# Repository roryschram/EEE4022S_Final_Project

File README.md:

## LoRa Based Communication System for Radiosonde Applications
### By Rory Schram

Welcome to my final year project GitHub page. This project focussed on the design and implementation of a LoRa-based radiosonde module for a weather balloon. Project files can be found in their respective folders, including all software, schematics, and PCB designs, for the transmission and receiver modules.

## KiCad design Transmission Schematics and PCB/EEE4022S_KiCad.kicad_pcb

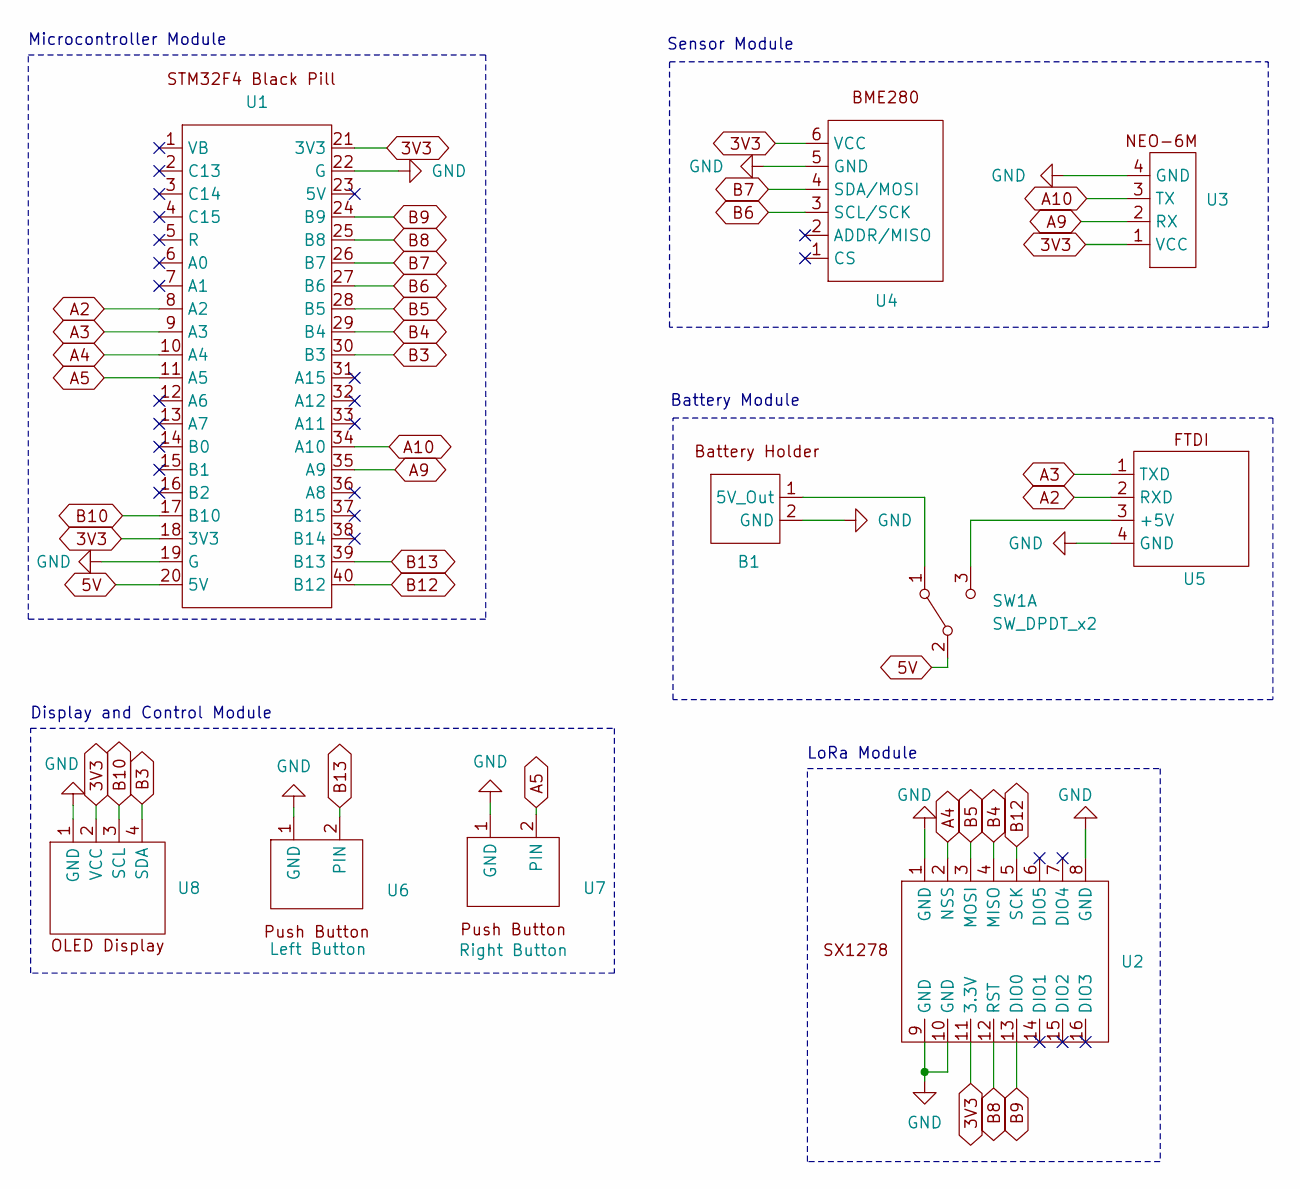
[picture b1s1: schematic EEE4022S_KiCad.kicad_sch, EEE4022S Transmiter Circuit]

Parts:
B1: Battery HolderCharger
SW1: SW_DPDT_x2
U1: STM32f4_Black_Pill
U2: SX1278
U3: NEO-6M
U4: BME280
U5: FTDI
U6: Left Button; Push Button
U7: Right Button; Push Button
U8: OLED Display

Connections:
3V3: U1.18 (3V3), U1.21 (3V3), U2.11 (3.3V), U3.1 (VCC), U4.6 (VCC), U8.2 (VCC)
5V: B1.1 (5V_Out), SW1.1 (A), SW1.2 (B), SW1.3 (C), U1.20 (5V), U5.3 (+5V)
A2: U1.8 (A2), U5.2 (RXD)
A3: U1.9 (A3), U5.1 (TXD)
A4: U1.10 (A4), U2.2 (NSS)
A5: U1.11 (A5), U7.2 (PIN)
A9: U1.35 (A9), U3.2 (RX)
A10: U1.34 (A10), U3.3 (TX)
B3: U1.30 (B3), U8.4 (SDA)
B4: U1.29 (B4), U2.4 (MISO)
B5: U1.28 (B5), U2.3 (MOSI)
B6: U1.27 (B6), U4.3 (SCL/SCK)
B7: U1.26 (B7), U4.4 (SDA/MOSI)
B8: U1.25 (B8), U2.12 (RST)
B9: U1.24 (B9), U2.13 (DIO0)
B10: U1.17 (B10), U8.3 (SCL)
B12: U1.40 (B12), U2.5 (SCK)
B13: U1.39 (B13), U6.2 (PIN)
GND: B1.2 (GND), U1.19 (G), U1.22 (G), U2.1 (GND), U2.8 (GND), U2.9 (GND), U2.10 (GND), U3.4 (GND), U4.5 (GND), U5.4 (GND), U6.1 (GND), U7.1 (GND), U8.1 (GND)

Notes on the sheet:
LoRa Module
Display and Control Module
Sensor Module
Microcontroller Module
Battery Module

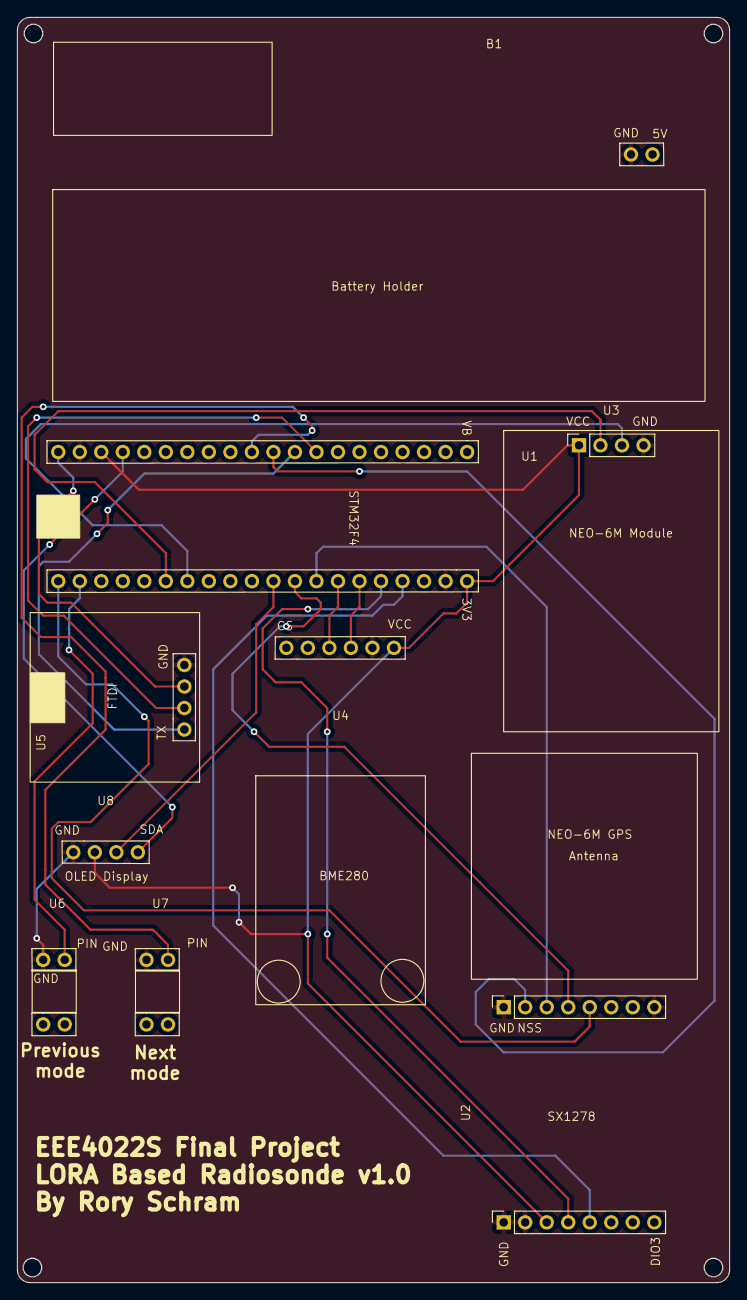
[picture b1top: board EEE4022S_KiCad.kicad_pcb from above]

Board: 2 copper layers, 84.0 x 149.3 mm, 9 parts (0 on the bottom side), 19 nets.

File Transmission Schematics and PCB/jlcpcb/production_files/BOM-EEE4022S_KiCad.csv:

Comment,Designator,Footprint,LCSC
~,U5,FTDI,
~,U3,NEO-6M,
Left Button,U6,Push Button,
~,U4,BME280,
Right Button,U7,Push Button,
~,B1,Battery HolderCharger,
~,U1,STM32f4_Black_Pill,
~,U8,OLED Display,
~,U2,SX1278,

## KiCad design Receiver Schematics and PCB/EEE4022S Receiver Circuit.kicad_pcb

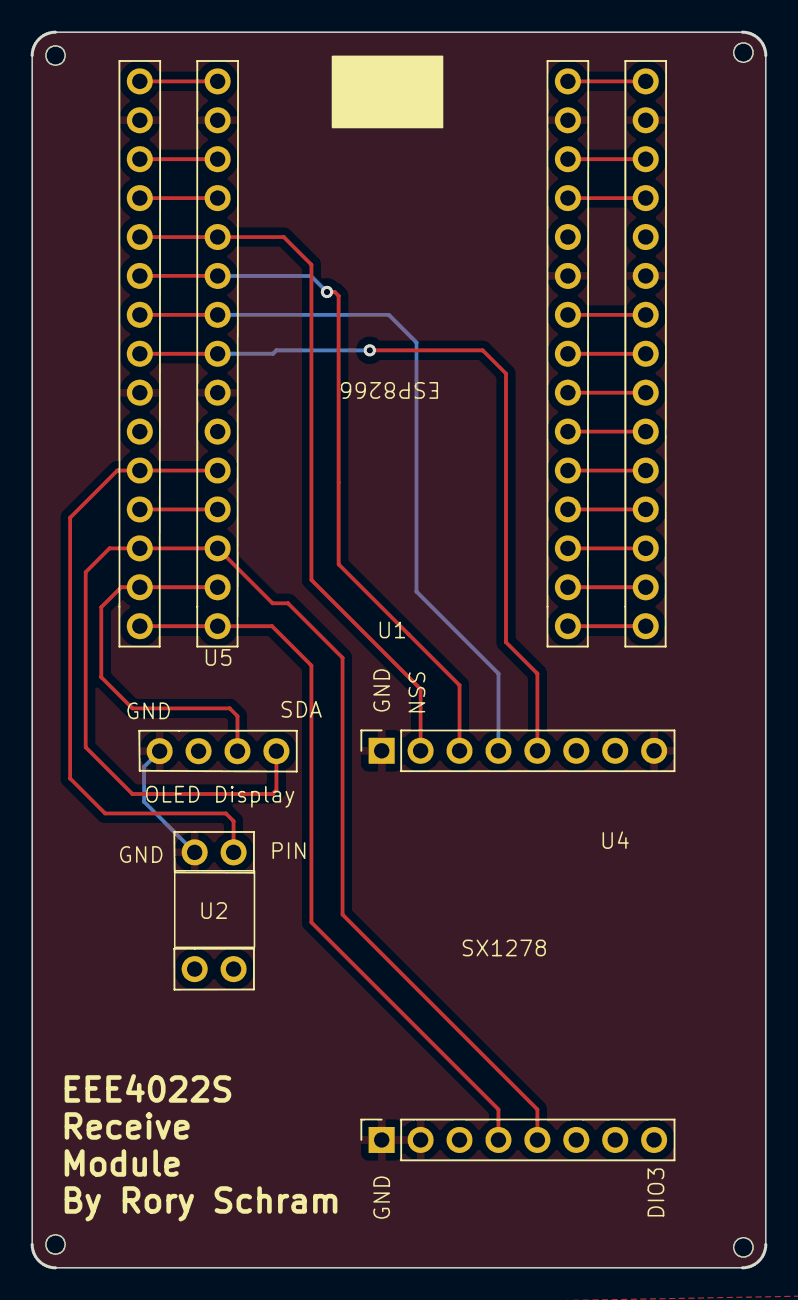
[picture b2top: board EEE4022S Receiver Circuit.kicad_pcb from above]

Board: 2 copper layers, 47.9 x 80.6 mm, 4 parts (0 on the bottom side), 10 nets.

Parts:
U1: ESP8266
U2: Navigator Button; Push Button
U4: SX1278
U5: OLED Display

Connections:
3V3: U1.11 (3V3), U1.21 (3V3), U4.11 (3.3V), U5.2 (VCC)
D0: U1.16 (D0), U4.12 (RST)
D1: U1.17 (D1), U5.3 (SCL)
D2: U1.18 (D2), U4.13 (DIO0), U5.4 (SDA)
D4: U1.20 (D4), U2.2 (PIN)
D5: U1.23 (D5), U4.5 (SCK)
D6: U1.24 (D6), U4.4 (MISO)
D7: U1.25 (D7), U4.3 (MOSI)
D8: U1.26 (D8), U4.2 (NSS)
GND: U1.10 (GND), U1.14 (GND), U1.22 (GND), U1.29 (GND), U2.1 (GND), U4.1 (GND), U4.8 (GND), U4.9 (GND), U4.10 (GND), U5.1 (GND)

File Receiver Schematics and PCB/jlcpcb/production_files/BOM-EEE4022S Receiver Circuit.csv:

Comment,Designator,Footprint,LCSC
~,U1,ESP8266,
~,U4,SX1278,
Navigator Button,U2,Push Button,
~,U5,OLED Display,

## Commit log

2023-09-21 First commit with GPS working
2023-09-21 Did a build on the code
2023-09-21 Implemented altitude measurement
2023-09-25 Transmission working perfectly now
2023-09-27 Fixed Lora Mdule with reset low issue
2023-10-04 Working Build
2023-10-05 Working System, now working on a timer
2023-10-05 Working again
2023-10-06 Fully working code excpet for mode 1
2023-10-23 Final code not cleaned up
2023-10-28 FInal Code
2023-10-30 Final transmitter code
2023-10-30 Cleaning up
2023-10-30 More cleaning up
